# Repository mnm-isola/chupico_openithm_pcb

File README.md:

WARNING: UNTESTED

This repository contains PCB design for a direct replacement to the Teensy LC version of OPENITHM board.

Origial build: https://github.com/Yona-W/OpeNITHM
Firmware: https://github.com/whowechina/chu_pico

Note: Capacitive touch *should* work out of the box, air sensors are inherently incompatible until someone write code that support it (into or fork the chu_pico firmware).

Note 2: Size of PCB is slightly longer to accommodate the Pi Pico's length, may not fit into the original OPENITHM's 3D printed case without modification, bottom screw holes have been moved down.

## List of Electronics

| Parts		|      Link      |  Qty|
|----------|:-------------:|------:|
| Raspberry Pi Pico (Preferably a pin-compatible clone with USB-C)|Aliexpress|1|
| Pi Pico Breakout Board 						|[Gerber file (.zip)](/chupico_openithm/gerber/)|1| 
| 74HC4051 Multiplexer Breakout Board 			|[Aliexpress](https://www.aliexpress.com/item/32807771098.html)|1|
| MPR121 Breakout Board 						|Aliexpress|3|
| 51k ohm Resistor THT							|x|6|
| 33 ohm Resistor THT							|x|3|
| 2.54mm Pin Header, Right Angle, 2 row, 24 pos	|[LCSC](https://lcsc.com/product-detail/New-Arrivals_XFCN-PZ254R-12-24P_C492440.html)|2|
| 2.54mm Socket, Straight, 1 row, 20 pos		|x|2|

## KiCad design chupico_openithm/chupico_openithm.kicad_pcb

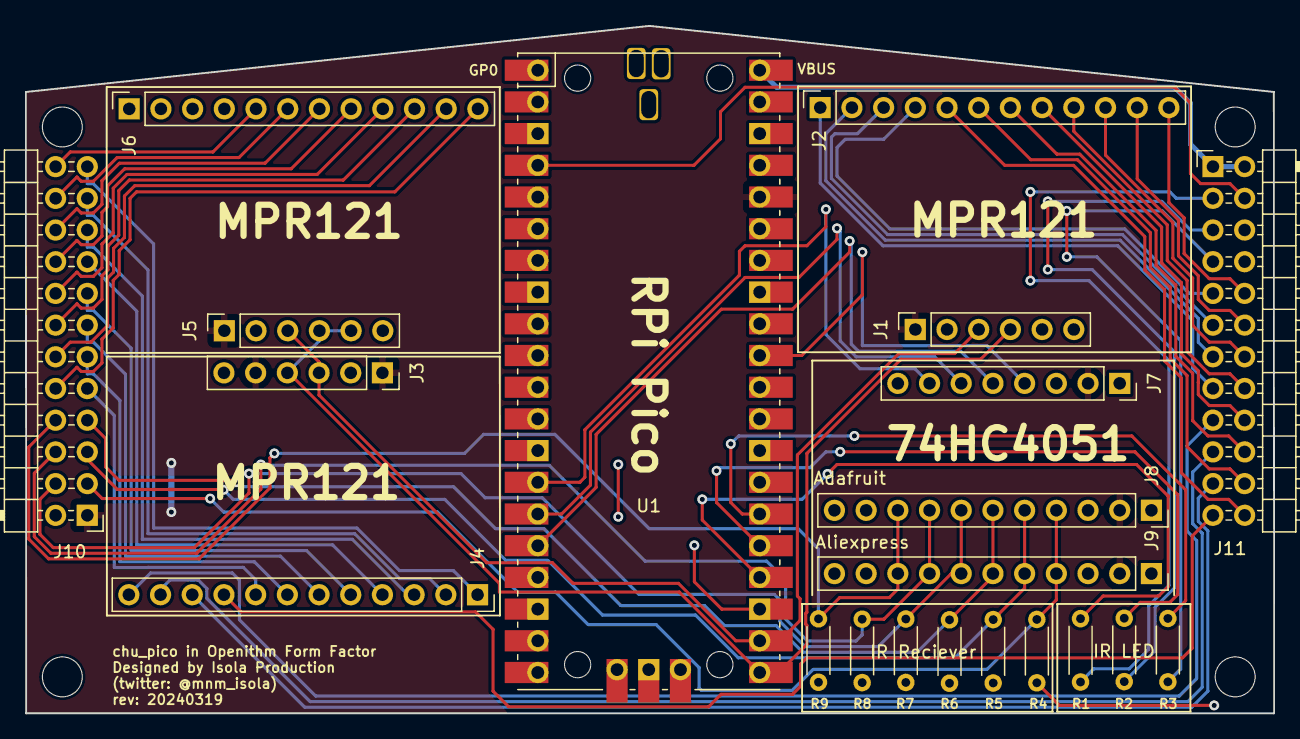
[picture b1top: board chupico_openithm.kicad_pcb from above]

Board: 2 copper layers, 100.0 x 55.1 mm, 25 parts (0 on the bottom side), 54 nets.

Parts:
J1, J3, J5: Conn_01x06; PinSocket_1x06_P2.54mm_Vertical
J2, J4, J6: Conn_01x12; PinSocket_1x12_P2.54mm_Vertical
J7: Conn_01x08; PinSocket_1x08_P2.54mm_Vertical
J8, J9: Conn_01x11; PinSocket_1x11_P2.54mm_Vertical
J10, J11: Conn_02x12_Odd_Even; PinHeader_2x12_P2.54mm_Horizontal
R1, R2, R3: 33; R_Axial_DIN0204_L3.6mm_D1.6mm_P5.08mm_Horizontal
R4, R5, R6, R7, R8, R9: R_AIR; R_Axial_DIN0204_L3.6mm_D1.6mm_P5.08mm_Horizontal
SCR1, SCR2, SCR3, SCR4: ScrewHole; MountingHole_3.2mm_M3
U1: Pico; RPi_Pico_SMD_TH

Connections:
+3V3: J1.1, J3.1, J3.5, J5.1, J7.2, J8.2, J9.2, J10.1, U1.36 (3V3)
+5V: J11.1, J11.2, U1.40 (VBUS)
/AIR_0: J8.4, J9.4, J10.3, R4.1
/AIR_1: J8.5, J9.5, J10.5, R5.1
/AIR_2: J8.6, J9.6, J10.7, R6.1
/AIR_3: J8.7, J9.7, J10.4, R7.1
/AIR_4: J8.8, J9.8, J10.6, R8.1
/AIR_5: J8.9, J9.9, J10.8, R9.1
/AIR_MUX_DATA: J7.4, U1.31 (GPIO26_ADC0)
/K1: J2.12, J11.10
/K2: J2.11, J11.12
/K3: J2.10, J11.14
/K4: J2.9, J11.16
/K5: J2.8, J11.18
/K6: J2.7, J11.20
/K7: J2.6, J11.22
/K8: J2.5, J11.24
/K9: J2.4, J11.9
/K10: J2.3, J11.11
/K11: J2.2, J11.13
/K12: J2.1, J11.15
/K13: J4.12, J11.17
/K14: J4.11, J11.19
/K15: J4.10, J11.21
/K16: J4.9, J11.23
/K17: J4.8, J10.9
/K18: J4.7, J10.11
/K19: J4.6, J10.13
/K20: J4.5, J10.15
/K21: J4.4, J10.17
/K22: J4.3, J10.19
/K23: J4.2, J10.21
/K24: J4.1, J10.23
/K25: J6.12, J10.10
/K26: J6.11, J10.12
/K27: J6.10, J10.14
/K28: J6.9, J10.16
/K29: J6.8, J10.18
/K30: J6.7, J10.20
/K31: J6.6, J10.22
/K32: J6.5, J10.24
/LED_0: R1.2, U1.24 (GPIO18)
/LED_0_OUT: J11.3, R1.1
/LED_1: R2.2, U1.25 (GPIO19)
/LED_1_OUT: J11.5, R2.1
/LED_2: R3.2, U1.26 (GPIO20)
/LED_2_OUT: J11.7, R3.1
/MUX_0: J7.5, U1.16 (GPIO12)
/MUX_1: J7.6, U1.15 (GPIO11)
/MUX_2: J7.7, U1.14 (GPIO10)
/RGB_DO: J11.4, U1.4 (GPIO2)
/SCL: J1.3, J3.3, J5.3, U1.22 (GPIO17)
/SDA: J1.4, J3.4, J5.4, J5.5, U1.21 (GPIO16)
GND: J1.5, J1.6, J3.6, J5.6, J7.1, J7.3, J7.8, J8.1, J8.3, J9.1, J9.3, J10.2, J11.6, J11.8, R4.2, R5.2, R6.2, R7.2, R8.2, R9.2, U1.3 (GND), U1.8 (GND), U1.13 (GND), U1.18 (GND), U1.23 (GND), U1.28 (GND), U1.33 (AGND), U1.38 (GND)

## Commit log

2024-03-19 upload first revisiom
2024-03-21 Update README.md
    Update README.md
